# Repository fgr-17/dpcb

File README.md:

# VOP24_LPCXpresso1769_baseHW #

### autor: Ing. Roux Federico G. (rouxfederico@gmail.com) ###

Desarrollo en KICAD del hardware base para LPCXpresso1769 con los componentes básicos:

	- regulación de tensión digital y analógica.
	- ads1292
	- slot microSD
	- salida serie para BT
	- medición de batería

## Historial ##

27.06.2018:

	- Creación del repositorio
    - se inicio el esquematico con dos reg mc1702, micro sd y medicion de bateria con lm358
    ...
    - se agrego simbolo del lpcxpresso1769
    - falta acomodar los directorios de las librerias
    - falta ads1292, simbolo y footprint
    - falta footprint lpcxpresso1769

29.06.2018:

    - conexiones con la SD y lpc1796
    - falta ads1292, simbolo y footprint
    - falta footprint lpcxpresso1769

30.06.2018:

    - se agrego simbolo ads1292 al esquematico
    - falta terminar las conexiones del ads
    - conviene separar en modulos jerarq. -> VER COMO SE HACE

PENDIENTES:

- ver modelo del diodo schottky del L4411
- ver footprint del micro USB b
- definir inductor acoplado

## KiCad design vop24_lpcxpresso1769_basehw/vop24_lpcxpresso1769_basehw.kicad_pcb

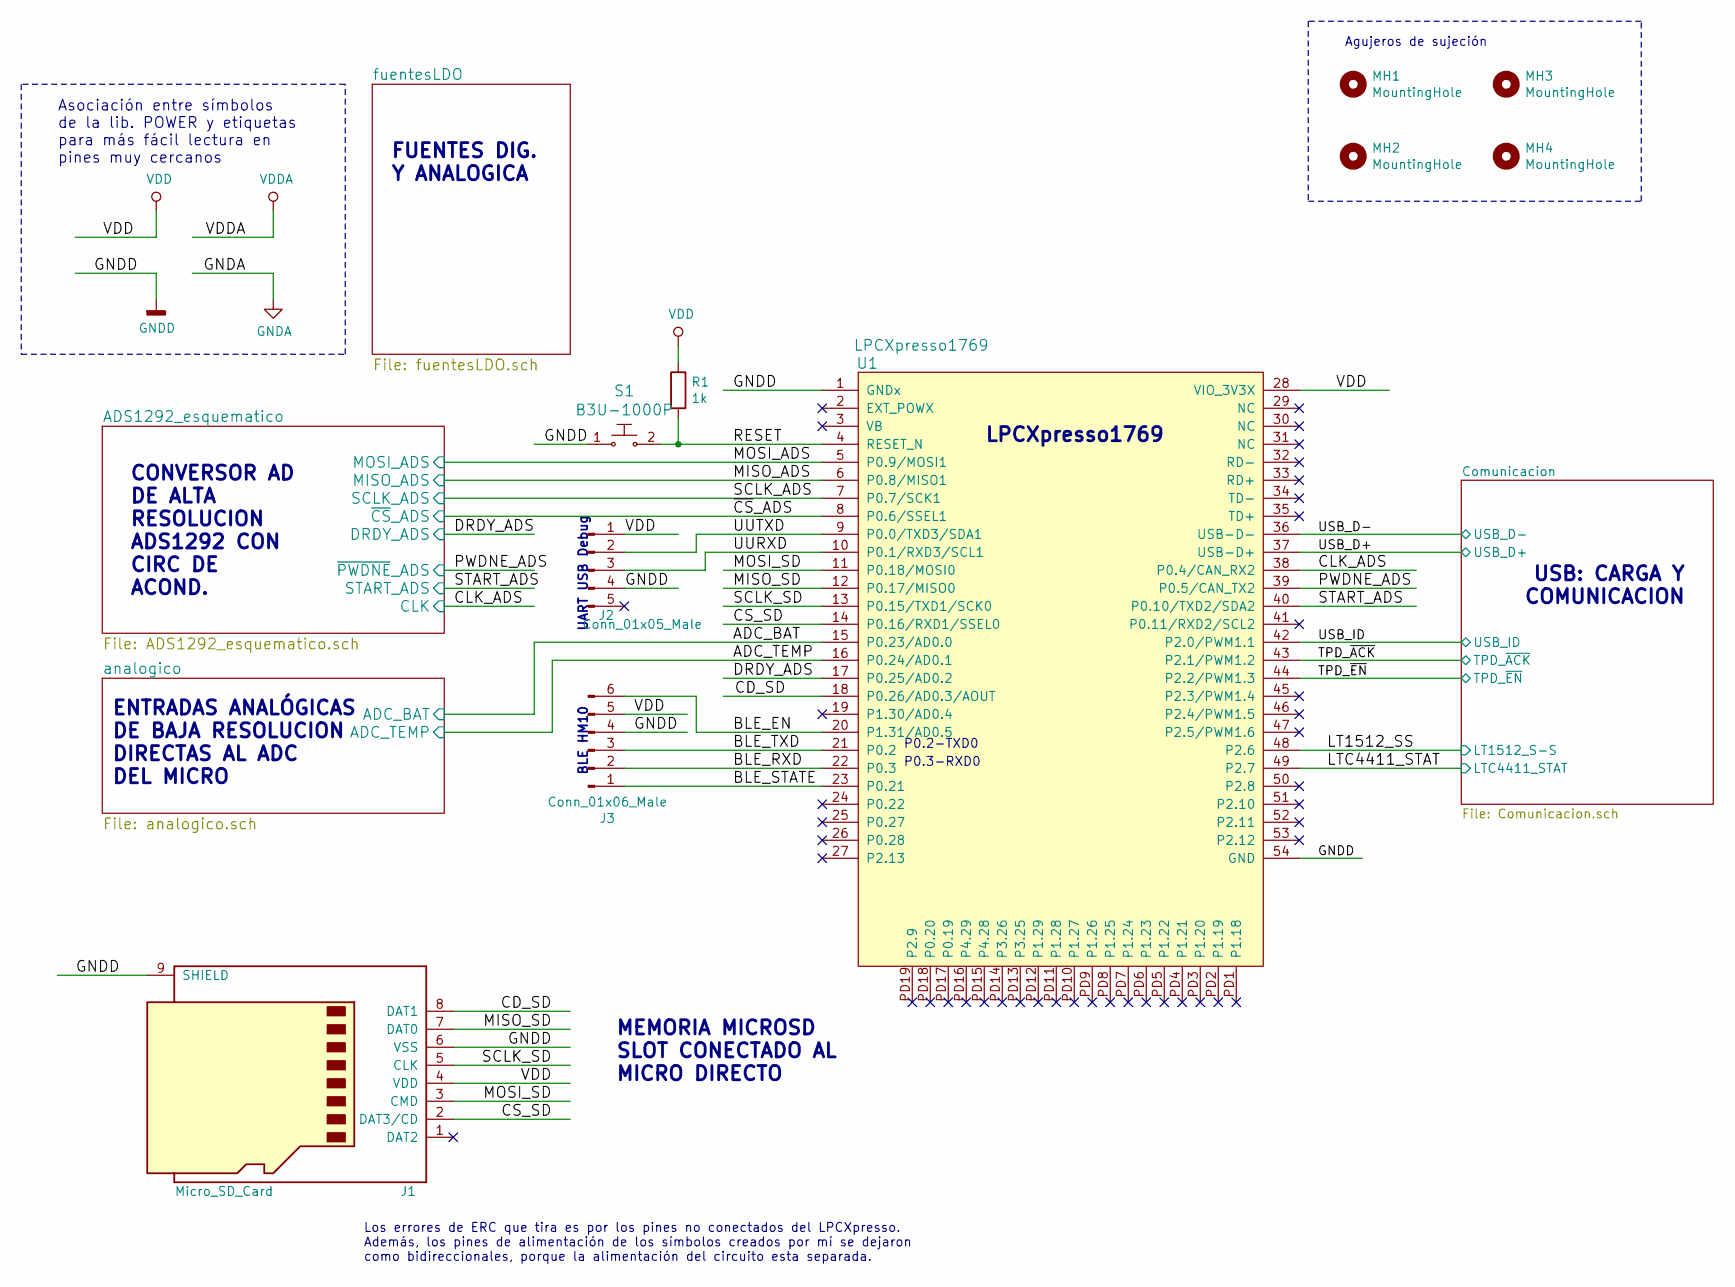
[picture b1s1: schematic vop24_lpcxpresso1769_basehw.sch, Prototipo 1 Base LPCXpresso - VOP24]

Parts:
J1: Micro_SD_Card; microSD_3020-901-0001-ACH-ELECTRONICS
J2: Conn_01x05_Male; PinSocket_1x05_P2.54mm_Vertical
J3: Conn_01x06_Male; PinSocket_1x06_P2.54mm_Vertical
MH1, MH2, MH3, MH4: MountingHole; MountingHole_3.5mm
R1: 1k; R_0805_2012Metric_Pad1.15x1.40mm_HandSolder
S1: B3U-1000P; Switch_Tactile_SMD_B3U-1000P; MPN B3U-1000P; Digi-Key_PN SW1020CT-ND
U1: LPCXpresso1769

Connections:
/ADC_BAT: U1.15 (P0.23/AD0.0); also elsewhere on the board
/ADC_TEMP: U1.16 (P0.24/AD0.1); also elsewhere on the board
/BLE_EN: J3.6, U1.20 (P1.31/AD0.5)
/BLE_RXD: J3.2, U1.22 (P0.3)
/BLE_STATE: J3.1, U1.23 (P0.21)
/BLE_TXD: J3.3, U1.21 (P0.2)
/CD_SD: J1.8 (DAT1), U1.18 (P0.26/AD0.3/AOUT)
/CLK_ADS: U1.38 (P0.4/CAN_RX2); also elsewhere on the board
/CS_SD: J1.2 (DAT3/CD), U1.14 (P0.16/RXD1/SSEL0)
/DRDY_ADS: U1.17 (P0.25/AD0.2); also elsewhere on the board
/LT1512_SS: U1.48 (P2.6); also elsewhere on the board
/LTC4411_STAT: U1.49 (P2.7); also elsewhere on the board
/MISO_ADS: U1.6 (P0.8/MISO1); also elsewhere on the board
/MISO_SD: J1.7 (DAT0), U1.12 (P0.17/MISO0)
/MOSI_ADS: U1.5 (P0.9/MOSI1); also elsewhere on the board
/MOSI_SD: J1.3 (CMD), U1.11 (P0.18/MOSI0)
/PWDNE_ADS: U1.39 (P0.5/CAN_TX2); also elsewhere on the board
/RESET: R1.2, S1.2, U1.4 (RESET_N)
/SCLK_ADS: U1.7 (P0.7/SCK1); also elsewhere on the board
/SCLK_SD: J1.5 (CLK), U1.13 (P0.15/TXD1/SCK0)
/START_ADS: U1.40 (P0.10/TXD2/SDA2); also elsewhere on the board
/TPD_~ACK: U1.43 (P2.1/PWM1.2); also elsewhere on the board
/TPD_~EN: U1.44 (P2.2/PWM1.3); also elsewhere on the board
/USB_D+: U1.37 (USB-D+); also elsewhere on the board
/USB_D-: U1.36 (USB-D-); also elsewhere on the board
/USB_ID: U1.42 (P2.0/PWM1.1); also elsewhere on the board
/UURXD: J2.3, U1.10 (P0.1/RXD3/SCL1)
/UUTXD: J2.2, U1.9 (P0.0/TXD3/SDA1)
/~CS~_ADS: U1.8 (P0.6/SSEL1); also elsewhere on the board
VDD: J1.4 (VDD), J2.1, J3.5, R1.1, U1.28 (VIO_3V3X); also elsewhere on the board

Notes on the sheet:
P0.2-TXD0
P0.3-RXD0
FUENTES DIG. Y ANALOGICA
ENTRADAS ANALÓGICAS DE BAJA RESOLUCION DIRECTAS AL ADC DEL MICRO
MEMORIA MICROSD SLOT CONECTADO AL MICRO DIRECTO
USB: CARGA Y COMUNICACION
CONVERSOR AD DE ALTA RESOLUCION ADS1292 CON CIRC DE ACOND.
LPCXpresso1769
Los errores de ERC que tira es por los pines no conectados del LPCXpresso. Además, los pines de alimentación de los símbolos creados por mí se dejaron como bidireccionales, porque la alimentación del circuito esta separada.
BLE HM10
UART USB Debug
Asociación entre símbolos de la lib. POWER y etiquetas para más fácil lectura en pines muy cercanos
Agujeros de sujeción

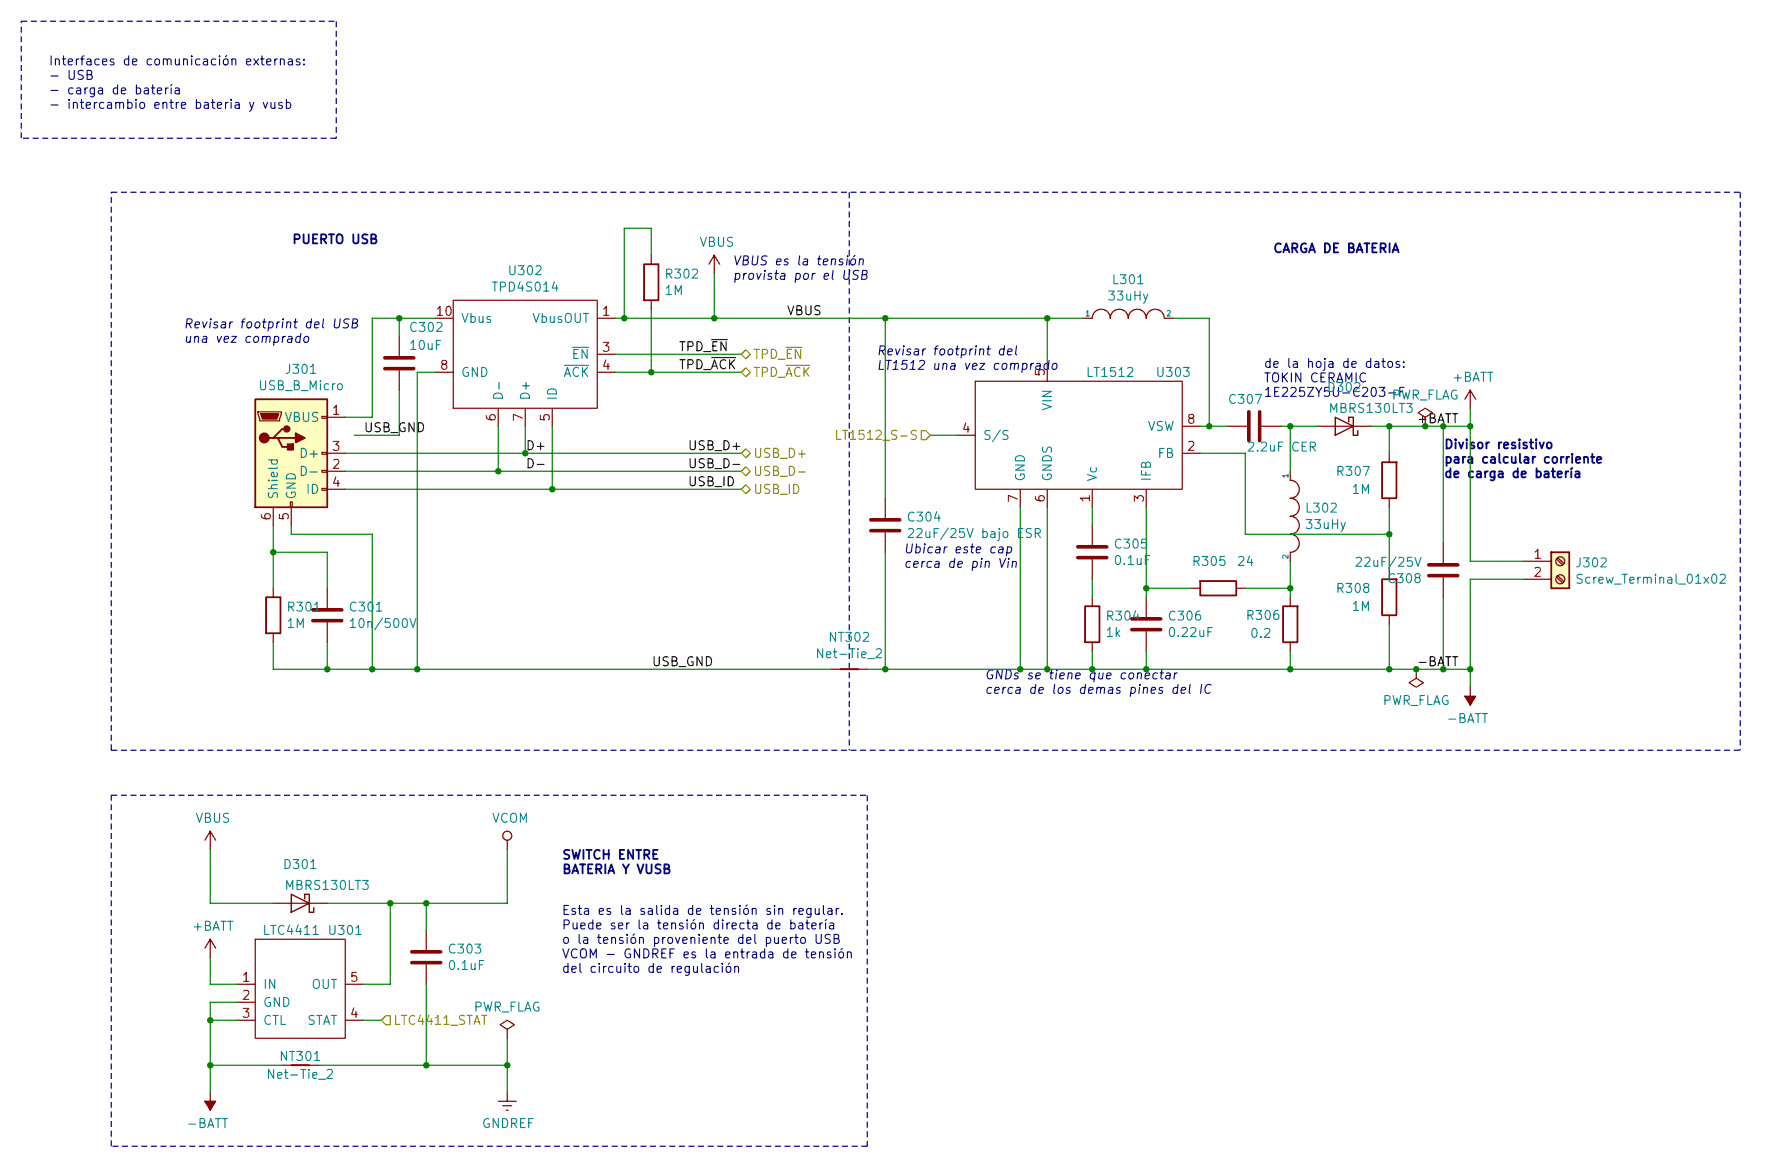
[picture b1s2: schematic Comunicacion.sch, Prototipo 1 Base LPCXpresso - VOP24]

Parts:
C301: 10n/500V; C_0805_2012Metric_Pad1.15x1.40mm_HandSolder
C302: 10uF; C_0805_2012Metric_Pad1.15x1.40mm_HandSolder
C303, C305: 0.1uF; C_0805_2012Metric_Pad1.15x1.40mm_HandSolder
C304: 22uF/25V bajo ESR; CP_Radial_D5.0mm_P2.50mm
C306: 0.22uF; C_0805_2012Metric_Pad1.15x1.40mm_HandSolder
C307: 2.2uF CER; CP_Radial_D5.0mm_P2.50mm
C308: 22uF/25V; CP_Radial_D5.0mm_P2.50mm
D301, D302: MBRS130LT3; D_SMB-SMC_Universal_Handsoldering
J301: USB_B_Micro; USB_Mini-B_Lumberg_2486_01_Horizontal
J302: Screw_Terminal_01x02; TerminalBlock_bornier-2_P5.08mm
L301, L302: 33uHy; L_Radial_D8.7mm_P5.00mm_Fastron_07HCP
NT301, NT302: Net-Tie_2; NetTie-2_SMD_Pad0.5mm
R301, R302, R307, R308: 1M; R_0805_2012Metric_Pad1.15x1.40mm_HandSolder
R304: 1k; R_0805_2012Metric_Pad1.15x1.40mm_HandSolder
R305: 24; R_0805_2012Metric_Pad1.15x1.40mm_HandSolder
R306: 0.2; R_0805_2012Metric_Pad1.15x1.40mm_HandSolder
U301: LTC4411; SOT-23-5_HandSoldering
U302: TPD4S014; Texas_S-PWSON-N10_ThermalVias
U303: LT1512; SO-8_5.3x6.2mm_P1.27mm

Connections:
+BATT: C308.2, D302.1 (K), J302.1, R307.2, U301.1 (IN); also elsewhere on the board
-BATT: C304.2, C306.2, C308.1, J302.2, NT301.1, NT302.2, R304.2, R306.1, R308.1, U301.2 (GND), U301.3 (CTL), U303.6 (GNDS), U303.7 (GND); also elsewhere on the board
/Comunicacion/USB_GND: C301.2, C302.2, J301.5 (GND), NT302.1, R301.2, U302.8 (GND)
/LT1512_SS: U303.4 (S/S); also elsewhere on the board
/LTC4411_STAT: U301.4 (STAT); also elsewhere on the board
/TPD_~ACK: R302.2, U302.4 (~ACK); also elsewhere on the board
/TPD_~EN: U302.3 (~EN); also elsewhere on the board
/USB_D+: J301.3 (D+), U302.7 (D+); also elsewhere on the board
/USB_D-: J301.2 (D-), U302.6 (D-); also elsewhere on the board
/USB_ID: J301.4 (ID), U302.5 (ID); also elsewhere on the board
GNDREF: C303.2, NT301.2; also elsewhere on the board
unnamed: C301.1, J301.6 (Shield), R301.1
unnamed: C302.1, J301.1 (VBUS), U302.10 (Vbus)
unnamed: C305.1, U303.1 (Vc)
unnamed: C305.2, R304.1
unnamed: C306.1, R305.2, U303.3 (IFB)
unnamed: C307.1, D302.2 (A), L302.1
unnamed: C307.2, L301.2, U303.8 (VSW)
unnamed: L302.2, R305.1, R306.2
unnamed: R307.1, R308.2, U303.2 (FB)
VBUS: C304.1, D301.2 (A), L301.1, R302.1, U302.1 (VbusOUT), U303.5 (VIN)
VCOM: C303.1, D301.1 (K), U301.5 (OUT); also elsewhere on the board

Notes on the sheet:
de la hoja de datos: TOKIN CERAMIC 1E225ZY5U-C203-F
Divisor resistivo para calcular corriente de carga de batería
CARGA DE BATERIA
SWITCH ENTRE BATERIA Y VUSB
PUERTO USB
Revisar footprint del USB una vez comprado
Revisar footprint del LT1512 una vez comprado
Ubicar este cap cerca de pin Vin
GNDs se tiene que conectar cerca de los demas pines del IC
Interfaces de comunicación externas: - USB - carga de batería - intercambio entre bateria y vusb
Esta es la salida de tensión sin regular. Puede ser la tensión directa de batería o la tensión proveniente del puerto USB VCOM - GNDREF es la entrada de tensión del circuito de regulación
VBUS es la tensión provista por el USB

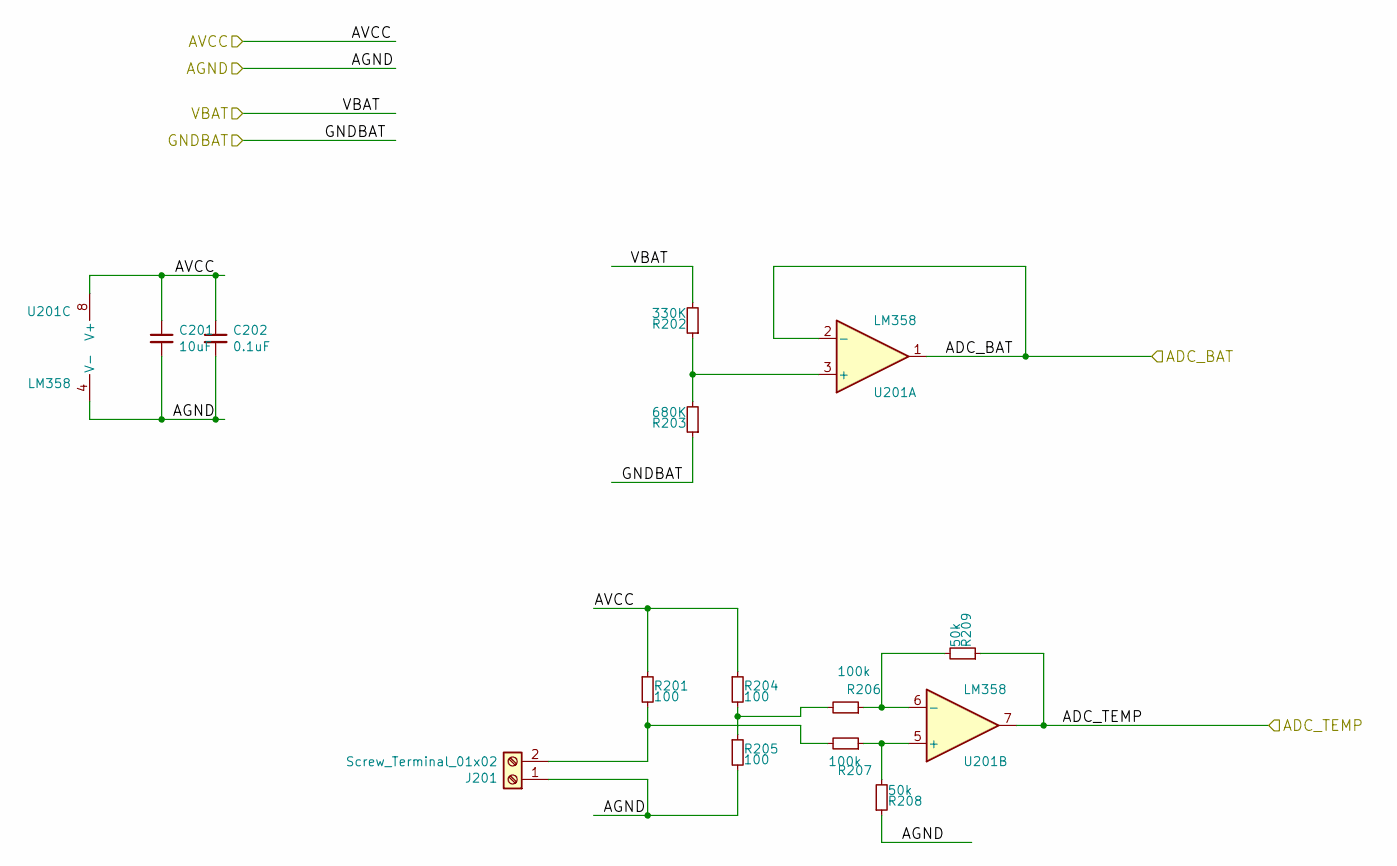
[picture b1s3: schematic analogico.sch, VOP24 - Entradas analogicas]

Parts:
C201: 10uF; C_0805_2012Metric_Pad1.15x1.40mm_HandSolder
C202: 0.1uF; C_0805_2012Metric_Pad1.15x1.40mm_HandSolder
J201: Screw_Terminal_01x02; TerminalBlock_bornier-2_P5.08mm
R201, R204, R205: 100; R_0805_2012Metric_Pad1.15x1.40mm_HandSolder
R202: 330K; R_0805_2012Metric_Pad1.15x1.40mm_HandSolder
R203: 680K; R_0805_2012Metric_Pad1.15x1.40mm_HandSolder
R206, R207: 100k; R_0805_2012Metric_Pad1.15x1.40mm_HandSolder
R208, R209: 50k; R_0805_2012Metric_Pad1.15x1.40mm_HandSolder
U201: LM358; SO-8_5.3x6.2mm_P1.27mm

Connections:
+BATT: R202.2; also elsewhere on the board
-BATT: R203.1; also elsewhere on the board
/ADC_BAT: U201.1, U201.2 (-); also elsewhere on the board
/ADC_TEMP: R209.1, U201.7; also elsewhere on the board
GNDA: C201.2, C202.2, J201.1, R205.2, R208.1, U201.4 (V-); also elsewhere on the board
unnamed: J201.2, R201.2, R207.2
unnamed: R202.1, R203.2, U201.3 (+)
unnamed: R204.2, R205.1, R206.2
unnamed: R206.1, R209.2, U201.6 (-)
unnamed: R207.1, R208.2, U201.5 (+)
VDDA: C201.1, C202.1, R201.1, R204.1, U201.8 (V+); also elsewhere on the board

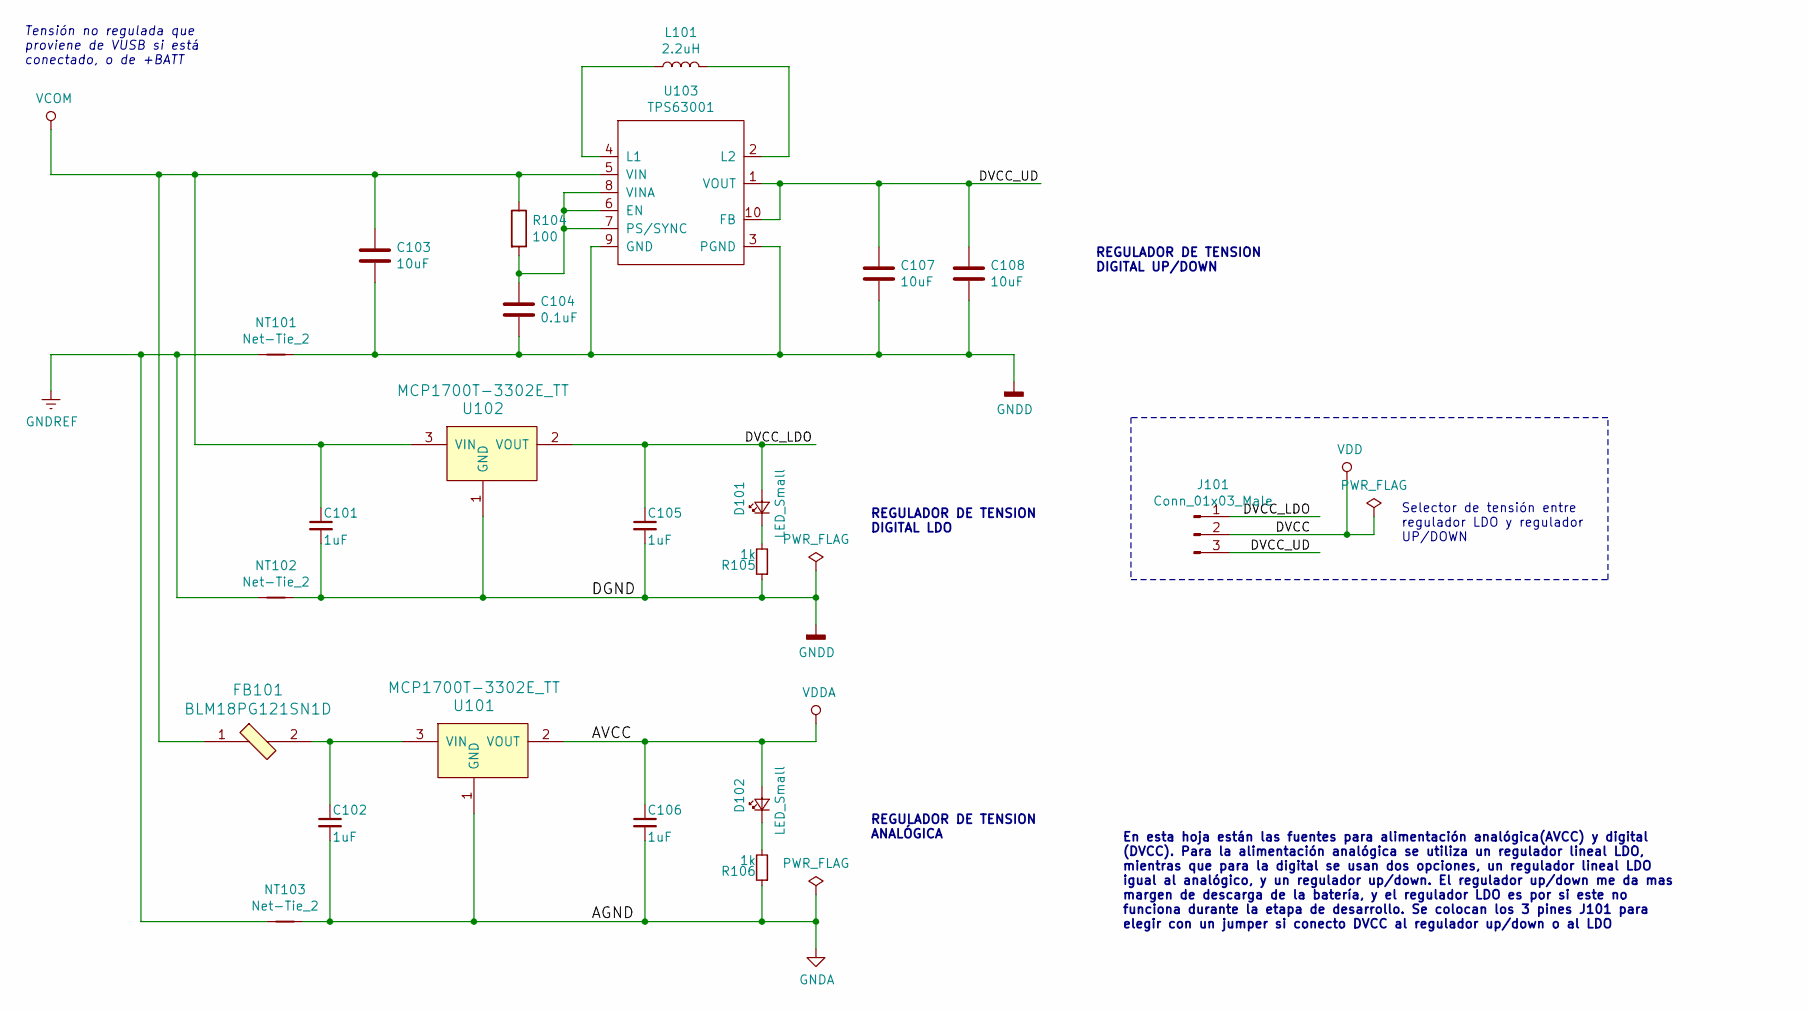
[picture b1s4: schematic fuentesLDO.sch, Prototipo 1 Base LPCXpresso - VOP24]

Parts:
C101, C102, C105, C106: 1uF; C_0805_2012Metric_Pad1.15x1.40mm_HandSolder
C103, C107, C108: 10uF; C_0805_2012Metric_Pad1.15x1.40mm_HandSolder
C104: 0.1uF; C_0805_2012Metric_Pad1.15x1.40mm_HandSolder
D101, D102: LED_Small; LED_0805_2012Metric_Pad1.15x1.40mm_HandSolder
FB101: BLM18PG121SN1D; 0603; MPN BLM18PG121SN1D; Digi-Key_PN 490-1037-1-ND
J101: Conn_01x03_Male; PinHeader_1x03_P2.54mm_Vertical
L101: 2.2uH; L_0805_2012Metric_Pad1.15x1.40mm_HandSolder
NT101, NT102, NT103: Net-Tie_2; NetTie-2_SMD_Pad0.5mm
R104: 100; R_0805_2012Metric_Pad1.15x1.40mm_HandSolder
R105, R106: 1k; R_0805_2012Metric_Pad1.15x1.40mm_HandSolder
U101, U102: MCP1700T-3302E_TT; SOT-23-3; MPN MCP1700T-3302E/TT; Digi-Key_PN MCP1700T3302ETTCT-ND
U103: TPS63001; VSON-10-1EP_3x3mm_P0.5mm_EP1.65x2.4mm_ThermalVias

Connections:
/fuentesLDO/DVCC_LDO: C105.1, D101.2 (A), J101.1, U102.2 (VOUT)
/fuentesLDO/DVCC_UD: C107.1, C108.1, J101.3, U103.1 (VOUT), U103.10 (FB)
GNDA: C102.2, C106.2, NT103.2, R106.1, U101.1 (GND); also elsewhere on the board
GNDREF: NT101.1, NT102.1, NT103.1; also elsewhere on the board
unnamed: C102.1, FB101.2, U101.3 (VIN)
unnamed: C104.1, R104.2, U103.6 (EN), U103.7 (PS/SYNC), U103.8 (VINA)
unnamed: D101.1 (K), R105.2
unnamed: D102.1 (K), R106.2
unnamed: L101.1, U103.4 (L1)
unnamed: L101.2, U103.2 (L2)
VCOM: C101.1, C103.1, FB101.1, R104.1, U102.3 (VIN), U103.5 (VIN); also elsewhere on the board
VDD: J101.2; also elsewhere on the board
VDDA: C106.1, D102.2 (A), U101.2 (VOUT); also elsewhere on the board

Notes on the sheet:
En esta hoja están las fuentes para alimentación analógica(AVCC) y digital (DVCC). Para la alimentación analógica se utiliza un regulador lineal LDO, mientras que para la digital se usan dos opciones, un regulador lineal LDO igual al analógico, y un regulador up/down. El regulador up/down me da mas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
Tensión no regulada que proviene de VUSB si está conectado, o de +BATT
REGULADOR DE TENSION ANALÓGICA
REGULADOR DE TENSION DIGITAL LDO
REGULADOR DE TENSION DIGITAL UP/DOWN
Selector de tensión entre regulador LDO y regulador UP/DOWN

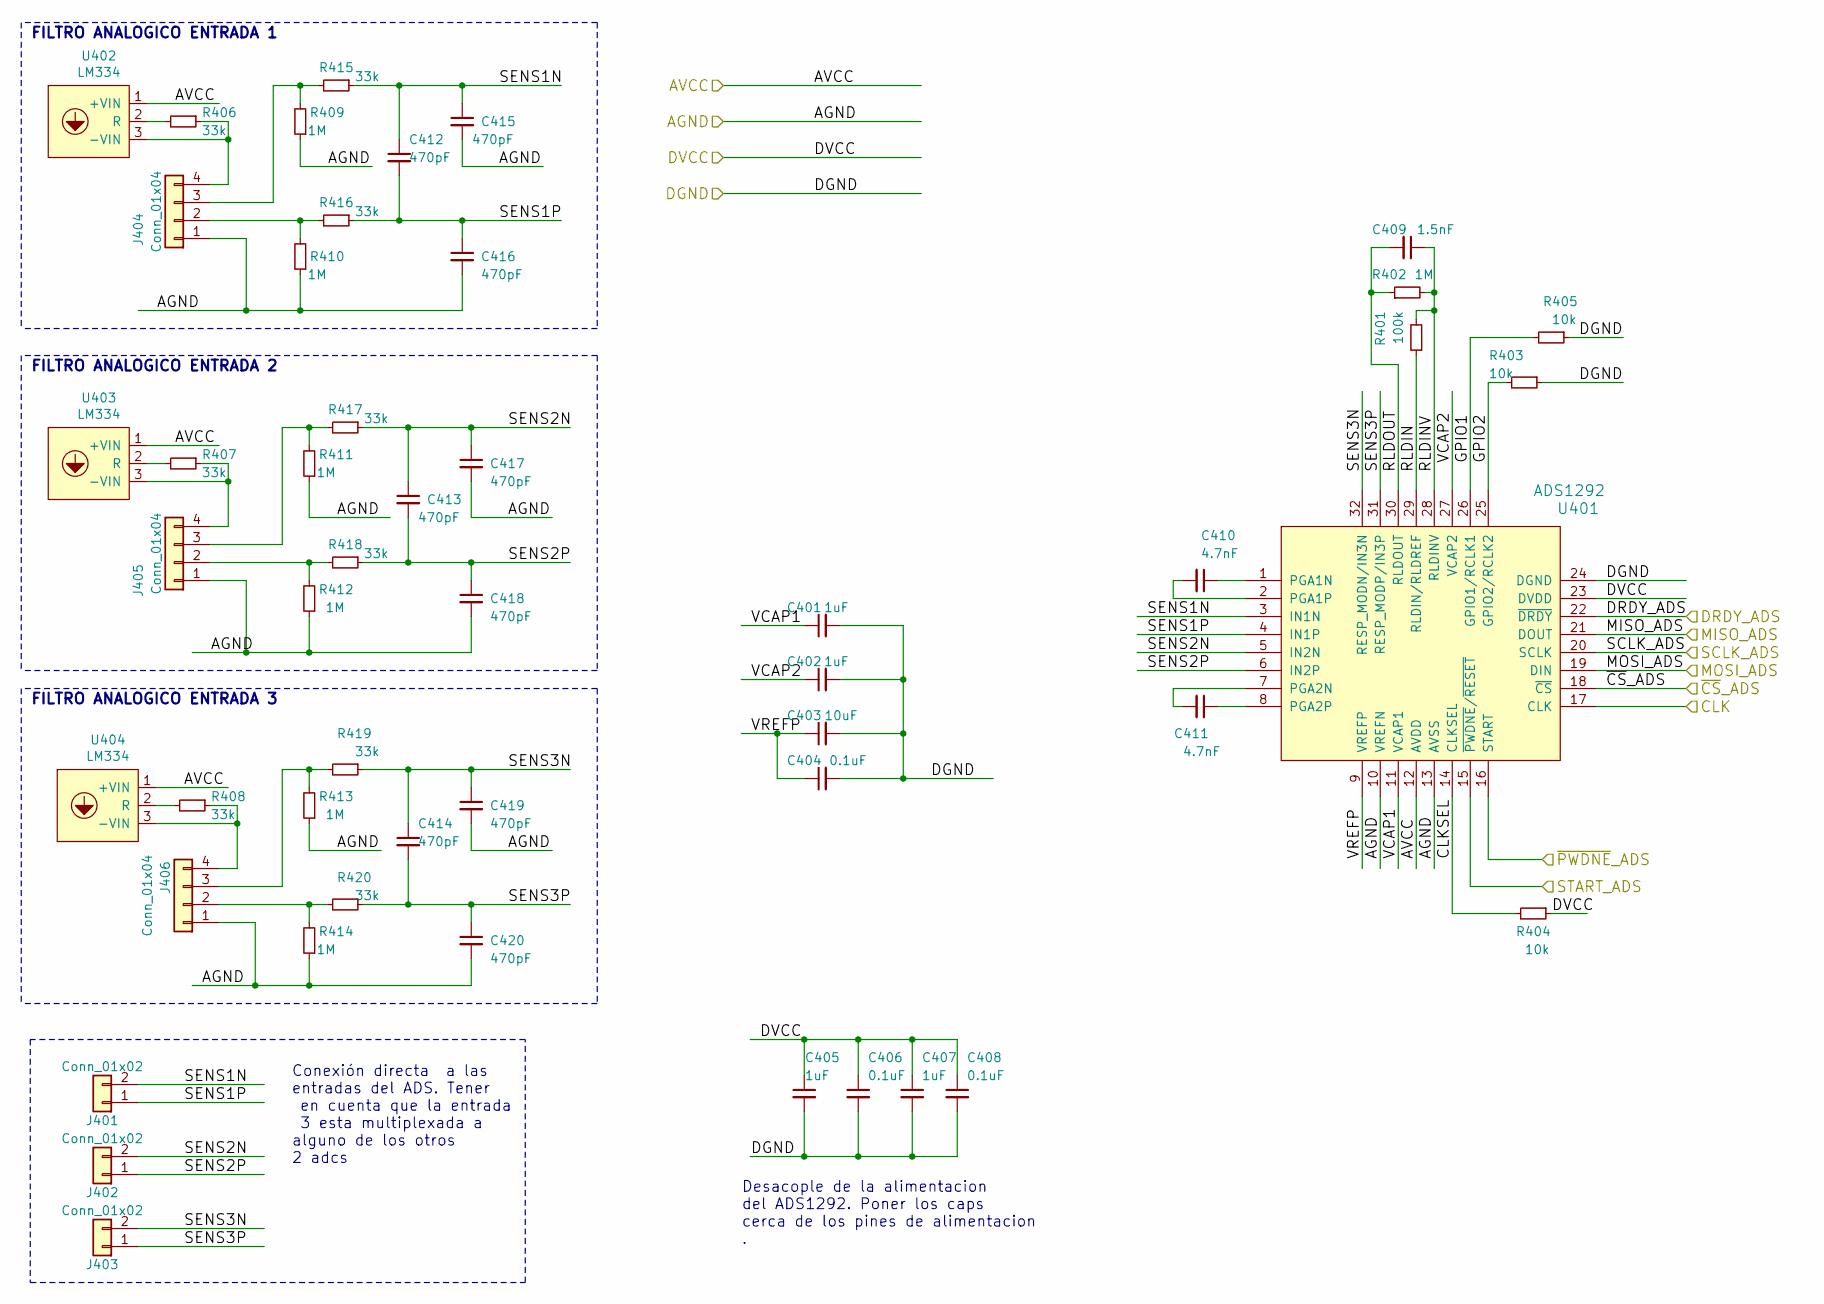
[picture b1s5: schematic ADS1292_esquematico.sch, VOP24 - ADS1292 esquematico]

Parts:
C401, C402, C405, C407: 1uF; C_0805_2012Metric_Pad1.15x1.40mm_HandSolder
C403: 10uF; C_0805_2012Metric_Pad1.15x1.40mm_HandSolder
C404, C406, C408: 0.1uF; C_0805_2012Metric_Pad1.15x1.40mm_HandSolder
C409: 1.5nF; C_0805_2012Metric_Pad1.15x1.40mm_HandSolder
C410, C411: 4.7nF; C_0805_2012Metric_Pad1.15x1.40mm_HandSolder
C412, C413, C414, C415, C416, C417, C418, C419, C420: 470pF; C_0805_2012Metric_Pad1.15x1.40mm_HandSolder
J401, J402, J403: Conn_01x02; PinHeader_1x02_P1.27mm_Vertical
J404, J405, J406: Conn_01x04; PinSocket_1x04_P2.54mm_Vertical
R401: 100k; R_0805_2012Metric_Pad1.15x1.40mm_HandSolder
R402, R409, R410, R411, R412, R413, R414: 1M; R_0805_2012Metric_Pad1.15x1.40mm_HandSolder
R403, R404, R405: 10k; R_0805_2012Metric_Pad1.15x1.40mm_HandSolder
R406, R407, R408, R415, R416, R417, R418, R419, R420: 33k; R_0805_2012Metric_Pad1.15x1.40mm_HandSolder
U401: ADS1292; PQFP-G32_7x7mm_P0.5mm
U402, U403, U404: LM334; TO-92_Inline_Wide

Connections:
/ADS1292_esquematico/CLKSEL: R404.2, U401.14 (CLKSEL)
/ADS1292_esquematico/GPIO1: R405.2, U401.26 (GPIO1/RCLK1)
/ADS1292_esquematico/GPIO2: R403.2, U401.25 (GPIO2/RCLK2)
/ADS1292_esquematico/RLDIN: R401.1, U401.29 (RLDIN/RLDREF)
/ADS1292_esquematico/RLDINV: C409.1, R401.2, R402.2, U401.28 (RLDINV)
/ADS1292_esquematico/RLDOUT: C409.2, R402.1, U401.30 (RLDOUT)
/ADS1292_esquematico/SENS1N: C412.1, C415.1, J401.2, R415.1, U401.3 (IN1N)
/ADS1292_esquematico/SENS1P: C412.2, C416.1, J401.1, R416.1, U401.4 (IN1P)
/ADS1292_esquematico/SENS2N: C413.1, C417.1, J402.2, R417.1, U401.5 (IN2N)
/ADS1292_esquematico/SENS2P: C413.2, C418.1, J402.1, R418.1, U401.6 (IN2P)
/ADS1292_esquematico/SENS3N: C414.1, C419.1, J403.2, R419.1, U401.32 (RESP_MODN/IN3N)
/ADS1292_esquematico/SENS3P: C414.2, C420.1, J403.1, R420.1, U401.31 (RESP_MODP/IN3P)
/CLK_ADS: U401.17 (CLK); also elsewhere on the board
/DRDY_ADS: U401.22 (~DRDY); also elsewhere on the board
/MISO_ADS: U401.21 (DOUT); also elsewhere on the board
/MOSI_ADS: U401.19 (DIN); also elsewhere on the board
/PWDNE_ADS: U401.16 (START); also elsewhere on the board
/SCLK_ADS: U401.20 (SCLK); also elsewhere on the board
/START_ADS: U401.15 (~PWDNE~/~RESET~); also elsewhere on the board
/~CS~_ADS: U401.18 (~CS); also elsewhere on the board
GNDA: C415.2, C416.2, C417.2, C418.2, C419.2, C420.2, J404.1, J405.1, J406.1, R409.1, R410.1, R411.1, R412.1, R413.1, R414.1, U401.10 (VREFN), U401.13 (AVSS); also elsewhere on the board
unnamed: C401.1, U401.11 (VCAP1)
unnamed: C402.1, U401.27 (VCAP2)
unnamed: C403.1, C404.1, U401.9 (VREFP)
unnamed: C410.1, U401.1 (PGA1N)
unnamed: C410.2, U401.2 (PGA1P)
unnamed: C411.1, U401.8 (PGA2P)
unnamed: C411.2, U401.7 (PGA2N)
unnamed: J404.2, R410.2, R416.2
unnamed: J404.3, R409.2, R415.2
unnamed: J404.4, R406.1, U402.3 (-VIN)
unnamed: J405.2, R412.2, R418.2
unnamed: J405.3, R411.2, R417.2
unnamed: J405.4, R407.1, U403.3 (-VIN)
unnamed: J406.2, R414.2, R420.2
unnamed: J406.3, R413.2, R419.2
unnamed: J406.4, R408.1, U404.3 (-VIN)
unnamed: R406.2, U402.2 (R)
unnamed: R407.2, U403.2 (R)
unnamed: R408.2, U404.2 (R)
VDD: C405.1, C406.1, C407.1, C408.1, R404.1, U401.23 (DVDD); also elsewhere on the board
VDDA: U401.12 (AVDD), U402.1 (+VIN), U403.1 (+VIN), U404.1 (+VIN); also elsewhere on the board

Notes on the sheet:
Conexión directa a las entradas del ADS. Tener en cuenta que la entrada 3 esta multiplexada a alguno de los otros 2 adcs
FILTRO ANALOGICO ENTRADA 1
FILTRO ANALOGICO ENTRADA 2
FILTRO ANALOGICO ENTRADA 3
Desacople de la alimentacion del ADS1292. Poner los caps cerca de los pines de alimentacion .

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
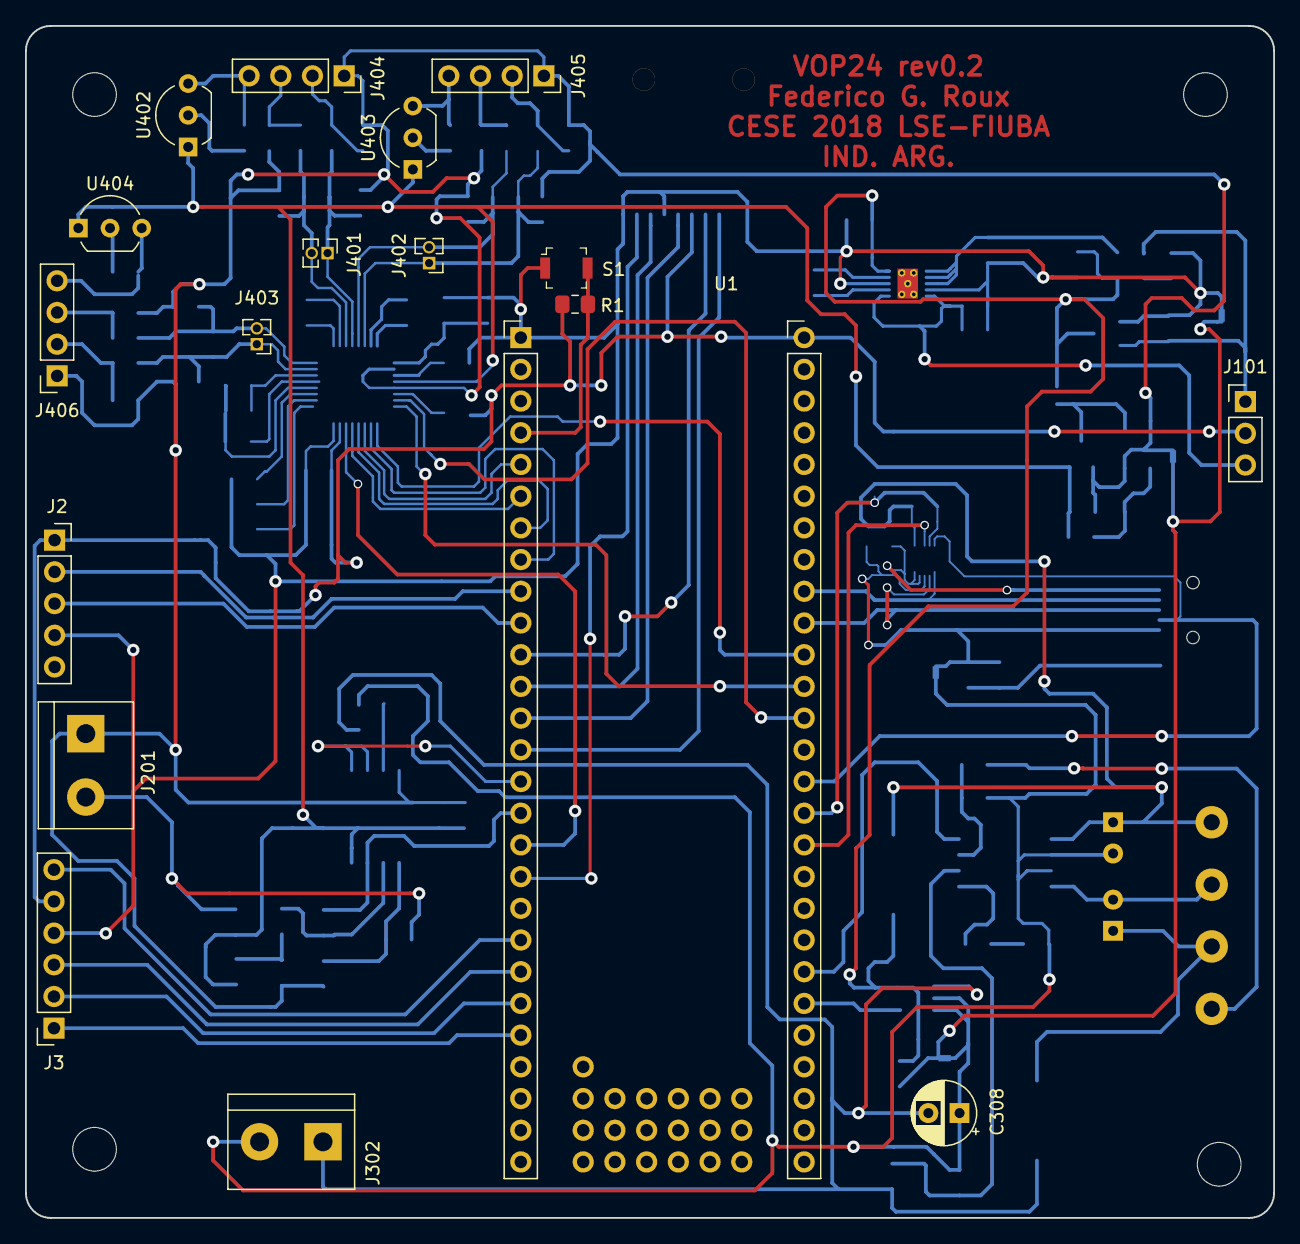
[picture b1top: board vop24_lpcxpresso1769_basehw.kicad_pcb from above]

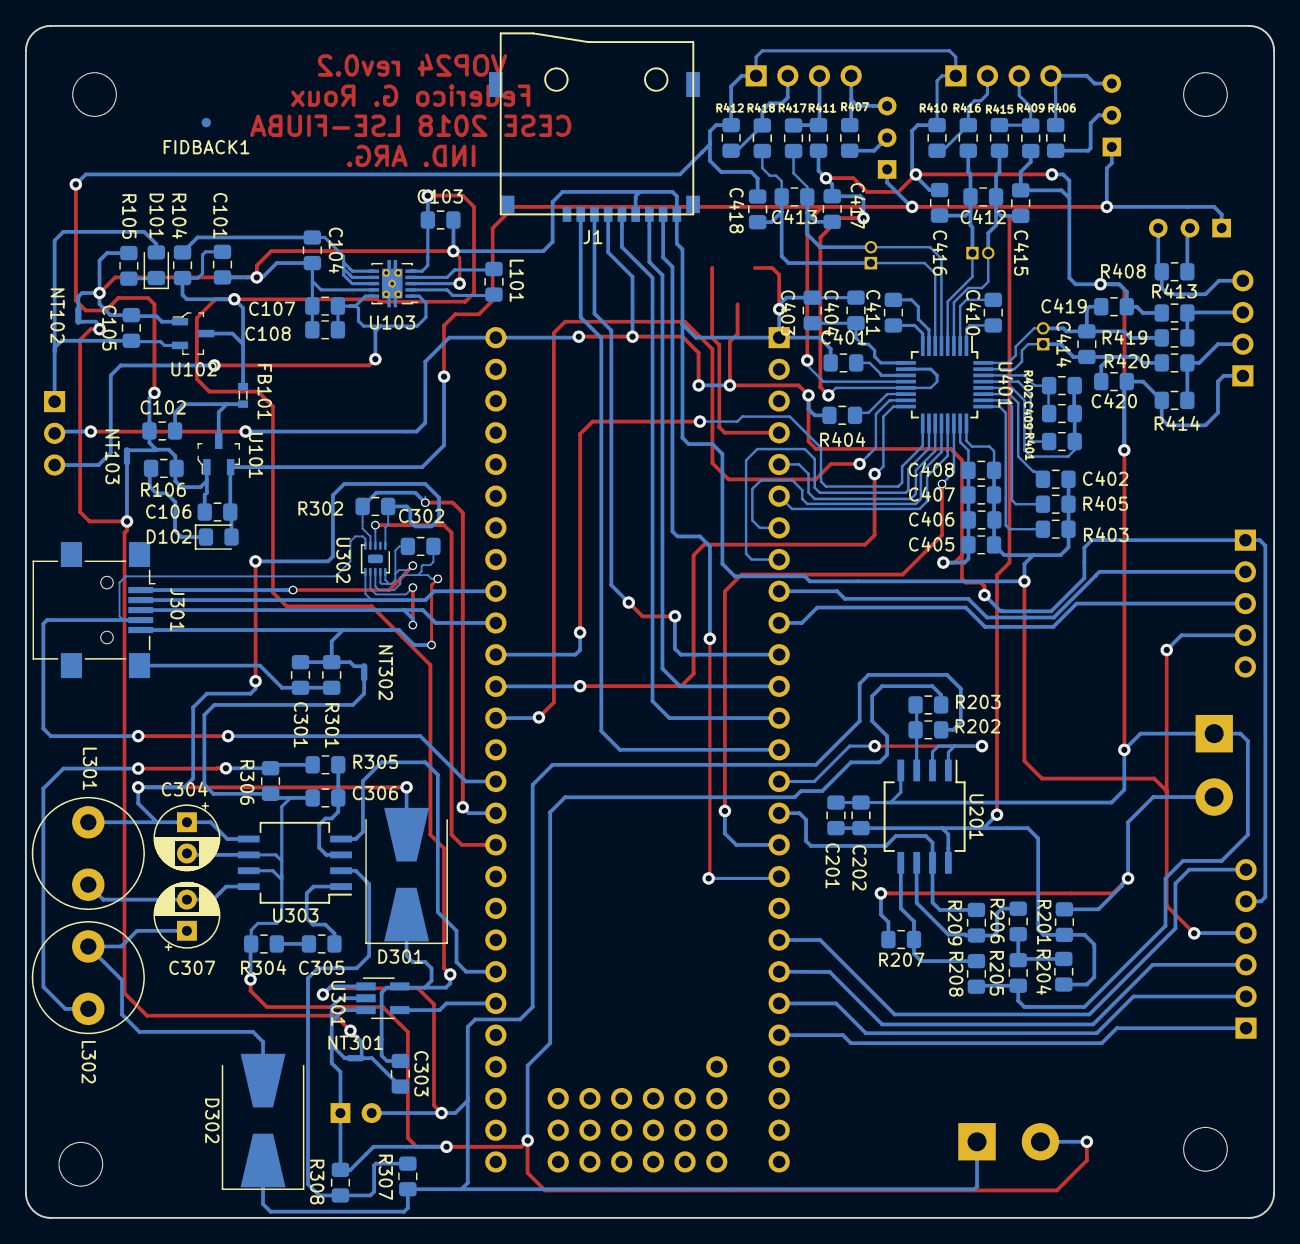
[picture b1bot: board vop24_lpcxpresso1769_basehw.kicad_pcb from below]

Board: 2 copper layers, 100.0 x 95.5 mm, 121 parts (99 on the bottom side), 92 nets.

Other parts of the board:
FIDBACK1: MountingHole; Fiducial_0.75mm_Dia_1.5mm_Outer

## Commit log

2018-06-27 Inicio del repo con README.md
2018-06-27 Inicio de esquematico con partes ppales. Falta completar y hacer simbolo y footprint de LPCXpresso1769
2018-06-28 Esquematico: - se agrego simbolo lpcxpresso1769
2018-06-30 Esquematico: - conexion SD con lpc1769
2018-06-30 Esquematico: - ads1292 con conexiones parcial
2018-07-01 Esquematico: - se paso el circuito de fuentes a una hoja aparte - falta pasar todas las demas a hojas separadas - terminar conexiones del ads - poner desacoples de alimentacion para cada IC - ver com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
2018-07-04 Esquematico: agregados hojas separadas de entradas analogicas terminadas y ads1292 sin terminar
2018-07-08 Esquematico: - terminar conexiones de ads: revisar slau387.pdf para conexiones de caps y bobinas - ver slau387.pdf para medicion de fuente y conexion usb
2018-07-09 Esquematico ADS1292: - invertir valor y nombre de todas las resistencias (puse el valor en el campo nombre :( ) - agregar protecciones y desacoples como en la nota de aplicacion - terminar filtros an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
2018-07-11 Esquematico ADS: - version a revisar. Falta agregar medicion de bateria y carga USB como en la nota de aplicacion
2018-09-18 Esquematico Comunicacion: falta agregar USB, BLE y UART
2018-09-28 Esq Comunicacion: USB, BLE y UART resueltos. Falta ver control de alimentación de BLE en caso que no se pueda apagar
2018-10-12 Primera versión esquematico sin revisar
2018-10-20 Algunas correcciones sobre el esquemático. Falta terminar de revisar algunos conflictos del DRC
2018-10-26 Correcciones de esquemático: - resueltos todos los conflictos de DRC - cambio de circutio de medicion de temp - ordenados todas las etiquetas y valores
2018-10-27 Se agregaron la mayoría de los footprints de los ICs
2018-11-01 Finalizada asociación de todos los footprints. Ver librerías froux-kicad
2018-11-03 Primer commit sobre el diseño del PCB. Se agruparon algunas hojas de esquemáticos. No se empezó a rutear
2018-11-11 PCB: componentes agrupados por zona
2018-11-11 Cambios menores en circuito ADS
2018-11-12 PCB: posicionamiento preruteo. ESQ: cambio de footprint de conectores
2018-11-13 PCB: ruteo e ubicacion de USB. ESQ: cambios de etiquetas de gnd en usb
2018-11-13 PCB: progreso en el ruteo
2018-11-14 PCB: ruteo de fuentes. SCH: separacion de pistas de masa en fuentes
2018-11-14 PCB: primera versión de ruteo finalizado sin poligonos. SCH: cambios de conexiones para facilitar conexiones
2018-11-14 PCB: ruteo finalizado con polígonos y texto en F.Cu. Agujeros en esquinas SCH: sin cambios
2018-11-14 PCB: agregado de leyenda de nombre de placa y revisión
2018-11-15 Agregado de leyendas en PCB y ESQ. Agregado de cotas en PCB
2018-11-22 ESQ: modificaciones grandes sobre correcciones del trabajo
2018-11-23 ESQ: cambios menores. Falta terminar de corregir
2018-11-23 ESQ: modificaciones menores
2018-11-23 ESQ: modificaciones de etiquetas. Falta cambiar todas las conexiones de vcc
2018-11-25 ESQ: cambios sobre etiquetas y simbolos de POWER
2018-11-27 ESQ: todas las correcciones atendidas
2018-11-27 ESQ: cambios en asociaciones de footprints
2018-11-27 actualizacion de PCB con cambios de ESQ
2018-11-28 ESQ: cambios en net-tie y footprints PCB: cambios grandes de dimensiones y ruteo
2018-11-29 ESQ: cambios menores PCB: finalizacion de ruteo con 0.3mm. Previo a poligonos
2018-11-29 Version entregada 2
